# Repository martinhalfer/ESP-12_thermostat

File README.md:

# ESP-12_thermostat

This project can be used as a Wi-Fi enabled PID temperature controller. It is designed for use in appliances through some sort of relay. - Originally an espresso machine. The software is designed to interface through an MQTT broker - I use mosquitto running on a Hass.io server.

The features are:

Hardware:<br>
3.3V onboard power supply<br>
ESP8266 (ESP12) module for wifi connectivity and processing.<br>
MAX31855 thermocouple amplifier.<br>
Screw terminals for AC power, thermocouple input and relay output.<br>
Breakout connectors for programming of the ESP8266 after assembly of the PCB.

Software:<br>
Temperature readout through SPI<br>
PID controlled duty cycle relay output<br>
MQTT temperature readout and setpoint setting.
Written in the Ardunio IDE

Mounting hardware:
Can be mounted to coffee machine with M3 standoffs. 3D printable mounting base model in repository

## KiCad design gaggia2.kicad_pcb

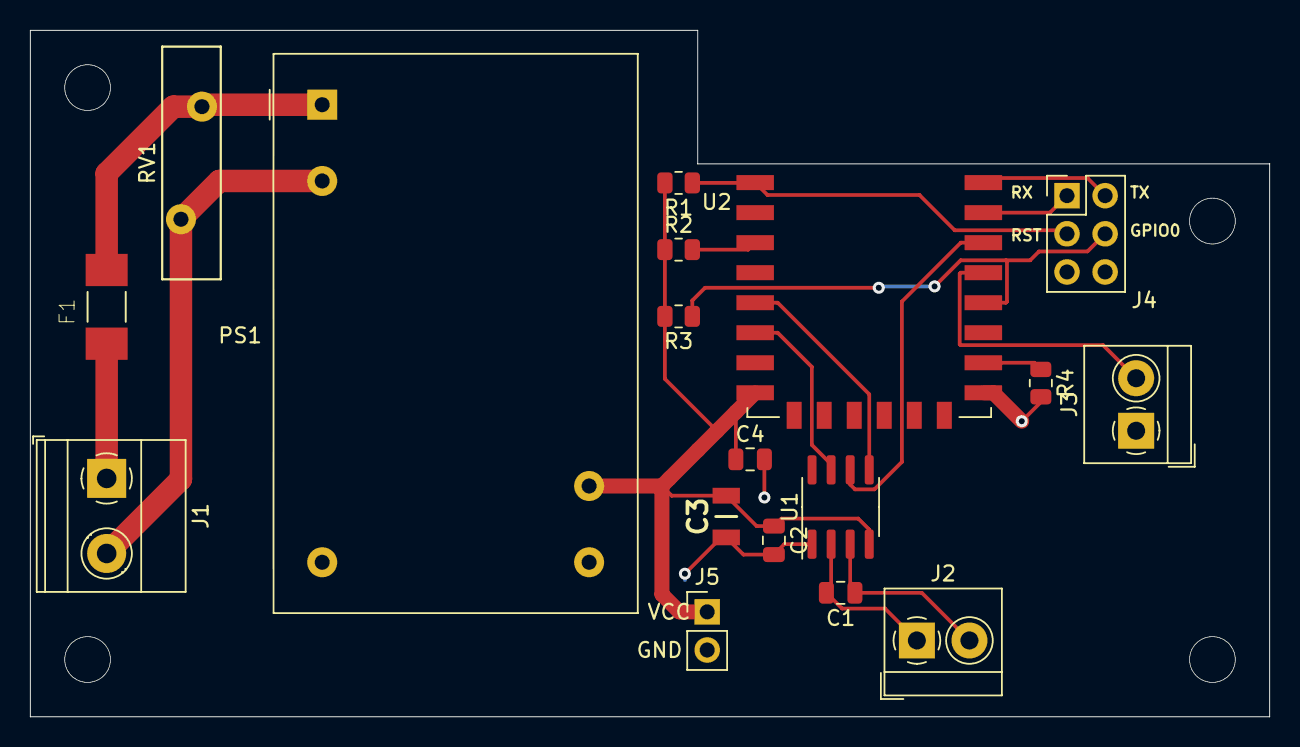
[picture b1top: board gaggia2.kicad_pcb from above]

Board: 2 copper layers, 82.5 x 45.7 mm, 18 parts (0 on the bottom side), 17 nets.

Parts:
C1, C2, C4: C_Small; C_0805_2012Metric
C3: C_Small; CAPC3216X160N
F1: Fuse; FUSC6125X279N
J1: Screw_Terminal_01x02; TerminalBlock_Phoenix_MKDS-1,5-2_1x02_P5.00mm_Horizontal
J2, J3: Screw_Terminal_01x02; TerminalBlock_4Ucon_1x02_P3.50mm_Horizontal
J4: Conn_02x03_Top_Bottom; PinHeader_2x03_P2.54mm_Vertical
J5: Conn_01x02_Male; PinHeader_1x02_P2.54mm_Vertical
PS1: RAC04-3.3SGA; Converter_ACDC_RECOM_RAC04-xxSGx_THT
R1, R2, R3, R4: R; R_0805_2012Metric
RV1: Varistor; RV_Disc_D15.5mm_W3.9mm_P7.5mm
U1: MAX31855KASA; SOIC-8_3.9x4.9mm_P1.27mm
U2: ESP-12E

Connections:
GND: C2.2, C3.2, C4.2, J3.1, J5.2, PS1.4, R4.2, U1.1, U2.15
unnamed: C1.1, J2.2, U1.3
unnamed: C1.2, J2.1, U1.2
unnamed: F1.1, J1.1
unnamed: F1.2, PS1.1, RV1.1
unnamed: J1.2, PS1.2, RV1.2
unnamed: J3.2, U2.19
unnamed: J4.1, U2.21
unnamed: J4.2, U2.22
unnamed: J4.3, R1.1, U2.1
unnamed: J4.4, R3.1, U2.18
unnamed: R2.2, U2.3
unnamed: R4.1, U2.16
unnamed: U1.5, U2.5
unnamed: U1.6, U2.20
unnamed: U1.7, U2.6
VCC: C2.1, C3.1, C4.1, J5.1, PS1.5, R1.2, R2.1, R3.2, U1.4, U2.8

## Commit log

2021-04-28 Update gaggia5.ino
    Added averaging function to clean up sensor data
2021-04-28 Add files via upload
    3D printable cover for high voltage side of Fotek solid state relay
2021-04-28 Add files via upload
    Housing base for PID controller. Isolates and protects high voltage leads.
2021-04-29 Bill of materials for PCB
2021-05-05 Update gaggia5.ino
    Improved sensor filtering and terminal output
